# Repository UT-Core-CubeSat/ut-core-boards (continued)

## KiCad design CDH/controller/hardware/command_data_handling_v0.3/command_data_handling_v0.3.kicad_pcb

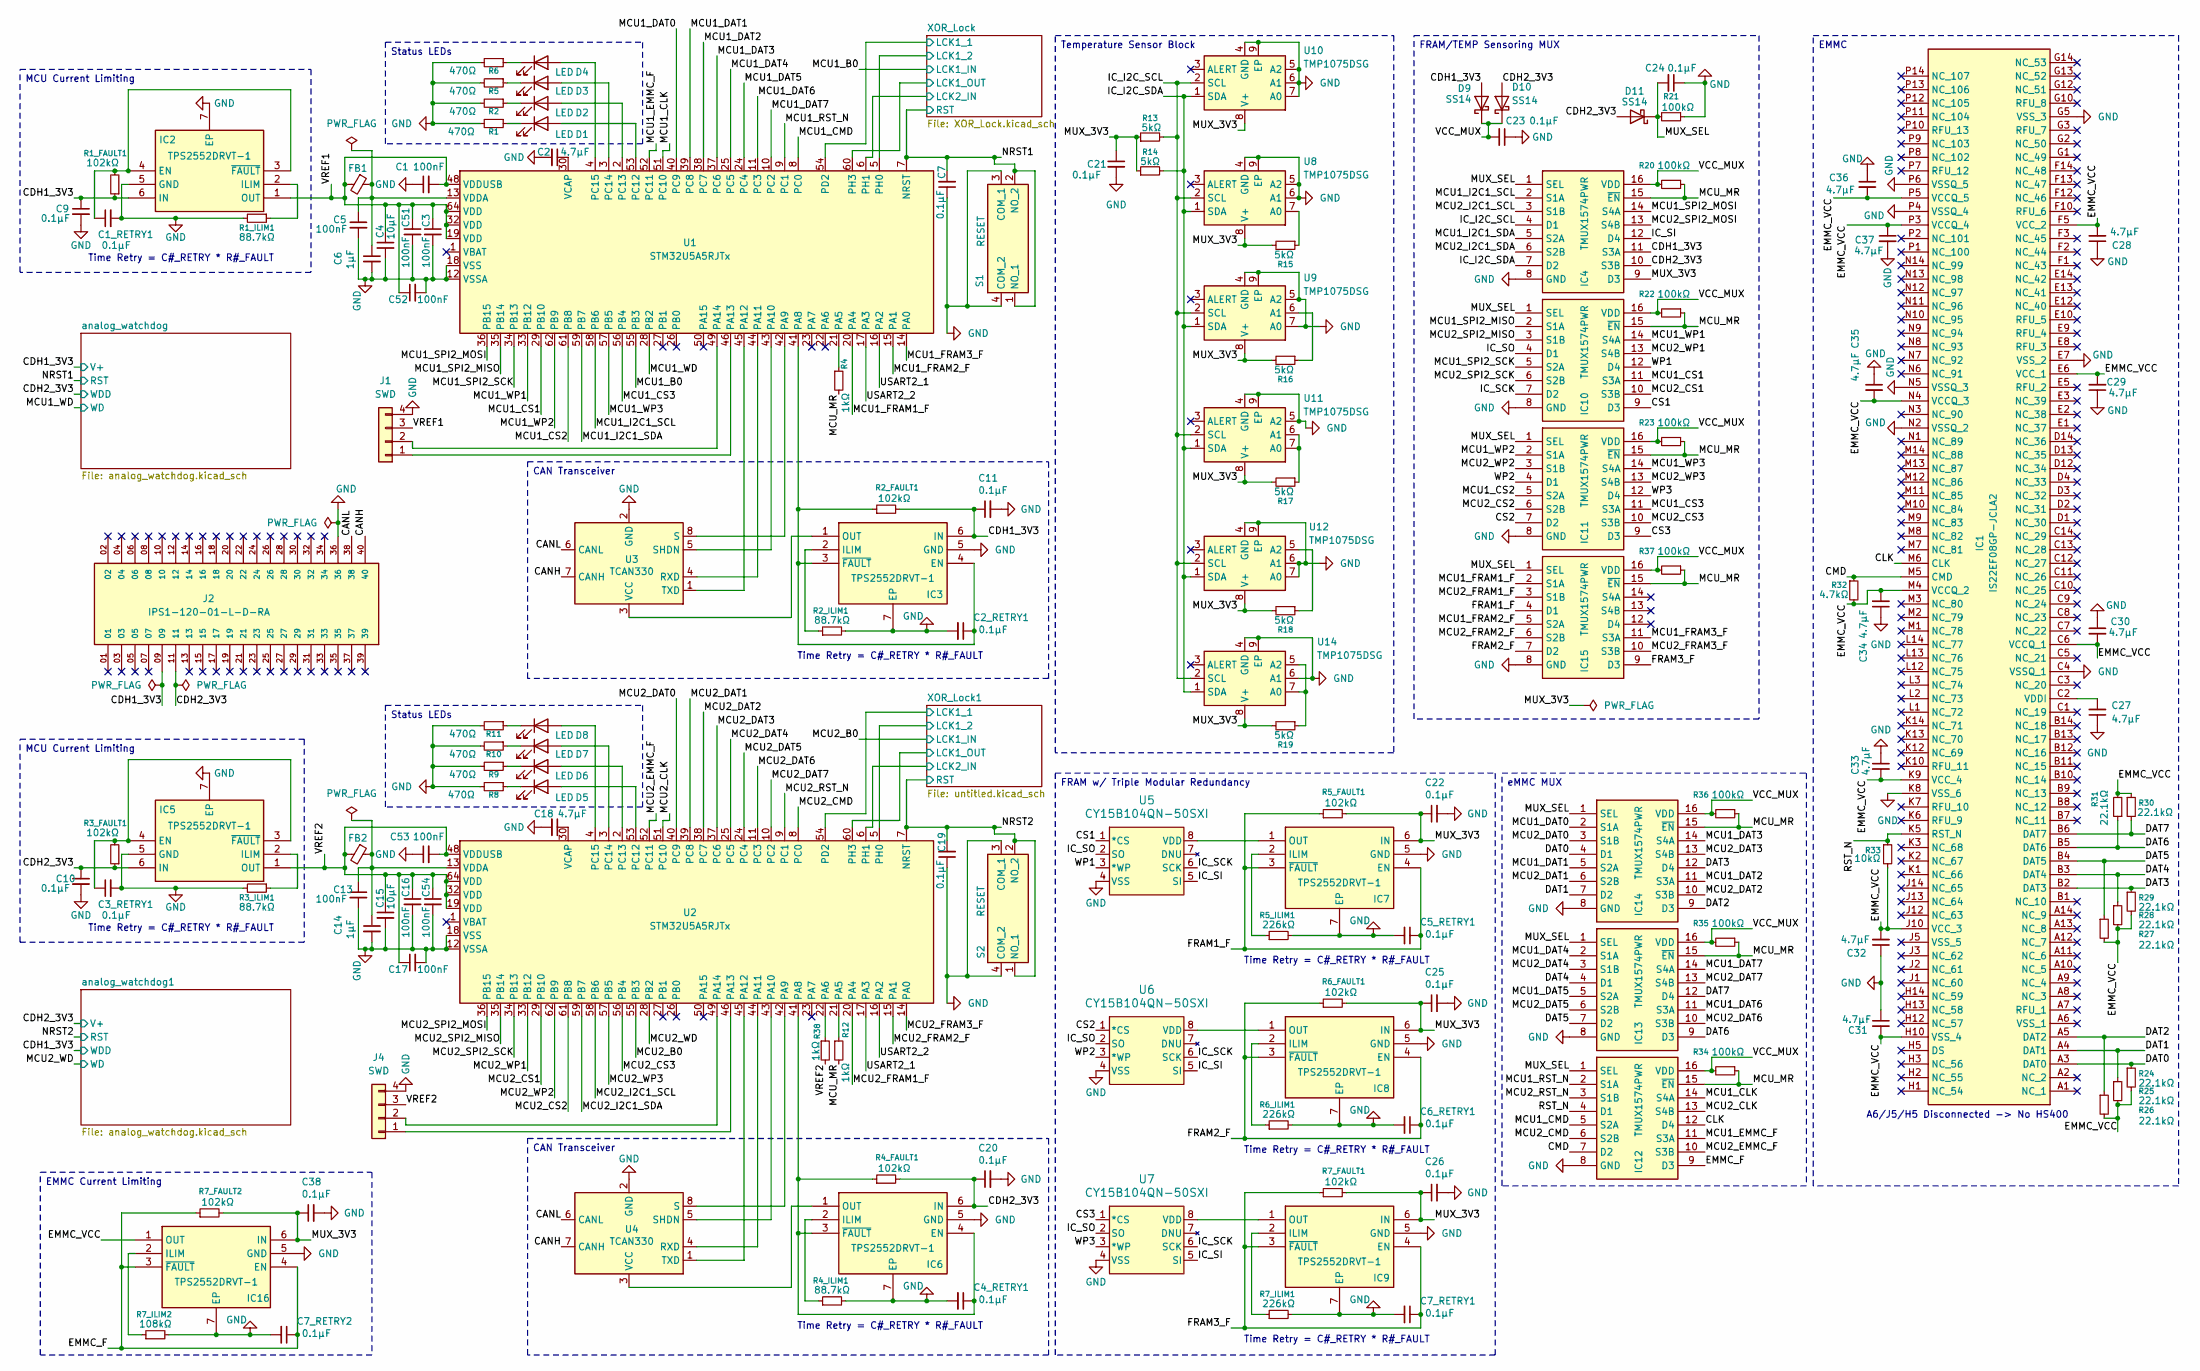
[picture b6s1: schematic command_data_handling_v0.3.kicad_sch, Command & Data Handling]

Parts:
C1, C3, C5, C13, C16, C17, C51, C52, C53, C54: 100nF; C_0603_1608Metric_Pad1.08x0.95mm_HandSolder
C1_RETRY1, C2_RETRY1, C3_RETRY1, C4_RETRY1, C5_RETRY1, C6_RETRY1, C7, C7_RETRY1, C7_RETRY2, C9, C10, C11, C19, C20, C21, C22, C23, C24, C25, C26, C38: 0.1µF; C_0603_1608Metric_Pad1.08x0.95mm_HandSolder
C2, C18, C27, C28, C29, C30, C31, C32, C33, C34, C35, C36, C37: 4.7µF; C_0805_2012Metric_Pad1.18x1.45mm_HandSolder
C4, C15: 10µF; C_0805_2012Metric_Pad1.18x1.45mm_HandSolder
C6, C14: 1µF; C_0805_2012Metric_Pad1.18x1.45mm_HandSolder
D1, D2, D3, D4, D5, D6, D7, D8: LED; LED_0201_0603Metric_Pad0.64x0.40mm_HandSolder
D9, D10, D11: SS14; D_SMA
FB1, FB2: FerriteBead_Small; R_0805_2012Metric_Pad1.20x1.40mm_HandSolder
IC1: IS22EF08GP-JCLA2; Mouser Part Number 870-IS22EF08GP-JCLA2
IC2, IC3, IC5, IC6, IC7, IC8, IC9, IC16: TPS2552DRVT-1; Mouser Part Number 595-TPS2552DRVT-1
IC4, IC10, IC11, IC12, IC13, IC14, IC15: TMUX1574PWR; Mouser Part Number 595-TMUX1574PWR
J1, J4: SWD; PinSocket_1x04_P2.54mm_Vertical
J2: IPS1-120-01-L-D-RA
R1, R2, R5, R6, R8, R9, R10, R11: 470Ω; R_0805_2012Metric_Pad1.20x1.40mm_HandSolder
R1_FAULT1, R2_FAULT1, R3_FAULT1, R4_FAULT1, R5_FAULT1, R6_FAULT1, R7_FAULT1, R7_FAULT2: 102kΩ; R_0805_2012Metric_Pad1.20x1.40mm_HandSolder
R1_ILIM1, R2_ILIM1, R3_ILIM1, R4_ILIM1: 88.7kΩ; R_0805_2012Metric_Pad1.20x1.40mm_HandSolder
R4, R12, R38: 1kΩ; R_0805_2012Metric_Pad1.20x1.40mm_HandSolder
R5_ILIM1, R6_ILIM1, R7_ILIM1: 226kΩ; R_0805_2012Metric_Pad1.20x1.40mm_HandSolder
R7_ILIM2: 108kΩ; R_0805_2012Metric_Pad1.20x1.40mm_HandSolder
R13, R14, R15, R16, R17, R18, R19: 5kΩ; R_0603_1608Metric_Pad0.98x0.95mm_HandSolder
R20, R21, R22, R23, R34, R35, R36, R37: 100kΩ; R_0805_2012Metric_Pad1.20x1.40mm_HandSolder
R24, R25, R26, R27, R28, R29, R30, R31: 22.1kΩ; R_0805_2012Metric_Pad1.20x1.40mm_HandSolder
R32: 4.7kΩ; R_0805_2012Metric_Pad1.20x1.40mm_HandSolder
R33: 10kΩ; R_0805_2012Metric_Pad1.20x1.40mm_HandSolder
S1, S2: RESET; KMR731NGLFS; Mouser Part Number 611-KMR731NGLFS
U1, U2: STM32U5A5RJTx; LQFP-64_10x10mm_P0.5mm
U3, U4: TCAN330; SOIC-8_3.9x4.9mm_P1.27mm
U5, U6, U7: CY15B104QN-50SXI
U8, U9, U10, U11, U12, U14: TMP1075DSG; WSON-8-1EP_2x2mm_P0.5mm_EP0.9x1.6mm_ThermalVias

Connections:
/CANH: J2.40, U3.7 (CANH), U4.7 (CANH)
/CANL: J2.38, U3.6 (CANL), U4.6 (CANL)
/CDH1_3V3: C9.1, C11.1, D9.2 (A), IC2.6 (IN), IC3.6 (IN), IC4.11 (S3A), J2.09, R1_FAULT1.1, R2_FAULT1.2; also elsewhere on the board
/CDH2_3V3: C10.1, C20.1, D10.2 (A), D11.2 (A), IC4.10 (S3B), IC5.6 (IN), IC6.6 (IN), J2.11, R3_FAULT1.1, R4_FAULT1.2; also elsewhere on the board
/CLK: IC1.M6 (CLK), IC12.12 (D4)
/CMD: IC1.M5 (CMD), IC12.7 (D2), R32.1
/CS1: IC10.9 (D3), U5.1 (*CS)
/CS2: IC11.7 (D2), U6.1 (*CS)
/CS3: IC11.9 (D3), U7.1 (*CS)
/DAT0: IC1.A3 (DAT0), IC14.4 (D1), R24.1
/DAT1: IC1.A4 (DAT1), IC14.7 (D2), R25.1
/DAT2: IC1.A5 (DAT2), IC14.9 (D3), R26.1
/DAT3: IC1.B2 (DAT3), IC14.12 (D4), R29.1
/DAT4: IC1.B3 (DAT4), IC13.4 (D1), R28.1
/DAT5: IC1.B4 (DAT5), IC13.7 (D2), R27.1
/DAT6: IC1.B5 (DAT6), IC13.9 (D3), R31.1
/DAT7: IC1.B6 (DAT7), IC13.12 (D4), R30.2
/EMMC_F: C7_RETRY2.1, IC12.9 (D3), IC16.3 (~FAULT), IC16.4 (EN), R7_FAULT2.1
/EMMC_VCC: C28.2, C29.2, C30.2, C31.2, C32.2, C33.2, C34.2, C35.2, C36.2, C37.1, IC1.C6 (VCCQ_1), IC1.E6 (VCC_1), IC1.F5 (VCC_2), IC1.H10 (VSS_4), IC1.J10 (VCC_3), IC1.K9 (VCC_4), IC1.M4 (VCCQ_2), IC1.N4 (VCCQ_3), IC1.P3 (VCCQ_4), IC1.P5 (VCCQ_5), IC16.1 (OUT), R24.2, R25.2, R26.2, R27.2, R28.2, R29.2, R30.1, R31.2, R32.2, R33.2
/FRAM1_F: C5_RETRY1.1, IC7.3 (~FAULT), IC7.4 (EN), IC15.4 (D1), R5_FAULT1.1
/FRAM2_F: C6_RETRY1.1, IC8.3 (~FAULT), IC8.4 (EN), IC15.7 (D2), R6_FAULT1.1
/FRAM3_F: C7_RETRY1.1, IC9.3 (~FAULT), IC9.4 (EN), IC15.9 (D3), R7_FAULT1.1
/IC_I2C_SCL: IC4.4 (D1), R13.2, U8.2 (SCL), U9.2 (SCL), U10.2 (SCL), U11.2 (SCL), U12.2 (SCL), U14.2 (SCL)
/IC_I2C_SDA: IC4.7 (D2), R14.2, U8.1 (SDA), U9.1 (SDA), U10.1 (SDA), U11.1 (SDA), U12.1 (SDA), U14.1 (SDA)
/IC_SCK: IC10.7 (D2), U5.6 (SCK), U6.6 (SCK), U7.6 (SCK)
/IC_SI: IC4.12 (D4), U5.5 (SI), U6.5 (SI), U7.5 (SI)
/IC_SO: IC10.4 (D1), U5.2 (SO), U6.2 (SO), U7.2 (SO)
/MCU1_B0: U1.55 (PB3); also elsewhere on the board
/MCU1_CLK: IC12.14 (S4A), U1.51 (PC10)
/MCU1_CMD: IC12.5 (S2A), U1.8 (PC0)
/MCU1_CS1: IC10.11 (S3A), U1.29 (PB10)
/MCU1_CS2: IC11.5 (S2A), U1.61 (PB8)
/MCU1_CS3: IC11.11 (S3A), U1.56 (PB4)
/MCU1_DAT0: IC14.2 (S1A), U1.40 (PC9)
/MCU1_DAT1: IC14.5 (S2A), U1.39 (PC8)
/MCU1_DAT2: IC14.11 (S3A), U1.38 (PC7)
/MCU1_DAT3: IC14.14 (S4A), U1.37 (PC6)
/MCU1_DAT4: IC13.2 (S1A), U1.25 (PC5)
/MCU1_DAT5: IC13.5 (S2A), U1.24 (PC4)
/MCU1_DAT6: IC13.11 (S3A), U1.11 (PC3)
/MCU1_DAT7: IC13.14 (S4A), U1.10 (PC2)
/MCU1_EMMC_F: IC12.11 (S3A), U1.52 (PC11)
/MCU1_FRAM1_F: IC15.2 (S1A), U1.20 (PA4)
/MCU1_FRAM2_F: IC15.5 (S2A), U1.15 (PA1)
/MCU1_FRAM3_F: IC15.11 (S3A), U1.14 (PA0)
/MCU1_I2C1_SCL: IC4.2 (S1A), U1.58 (PB6)
/MCU1_I2C1_SDA: IC4.5 (S2A), U1.59 (PB7)
/MCU1_RST_N: IC12.2 (S1A), U1.9 (PC1)
/MCU1_SPI2_MISO: IC10.2 (S1A), U1.35 (PB14)
/MCU1_SPI2_MOSI: IC4.14 (S4A), U1.36 (PB15)
/MCU1_SPI2_SCK: IC10.5 (S2A), U1.34 (PB13)
/MCU1_WD: U1.28 (PB2); also elsewhere on the board
/MCU1_WP1: IC10.14 (S4A), U1.33 (PB12)
/MCU1_WP2: IC11.2 (S1A), U1.62 (PB9)
/MCU1_WP3: IC11.14 (S4A), U1.57 (PB5)
/MCU2_B0: U2.55 (PB3); also elsewhere on the board
/MCU2_CLK: IC12.13 (S4B), U2.51 (PC10)
/MCU2_CMD: IC12.6 (S2B), U2.8 (PC0)
/MCU2_CS1: IC10.10 (S3B), U2.29 (PB10)
/MCU2_CS2: IC11.6 (S2B), U2.61 (PB8)
/MCU2_CS3: IC11.10 (S3B), U2.56 (PB4)
/MCU2_DAT0: IC14.3 (S1B), U2.40 (PC9)
/MCU2_DAT1: IC14.6 (S2B), U2.39 (PC8)
/MCU2_DAT2: IC14.10 (S3B), U2.38 (PC7)
/MCU2_DAT3: IC14.13 (S4B), U2.37 (PC6)
/MCU2_DAT4: IC13.3 (S1B), U2.25 (PC5)
/MCU2_DAT5: IC13.6 (S2B), U2.24 (PC4)
/MCU2_DAT6: IC13.10 (S3B), U2.11 (PC3)
/MCU2_DAT7: IC13.13 (S4B), U2.10 (PC2)
/MCU2_EMMC_F: IC12.10 (S3B), U2.52 (PC11)
/MCU2_FRAM1_F: IC15.3 (S1B), U2.20 (PA4)
/MCU2_FRAM2_F: IC15.6 (S2B), U2.15 (PA1)
/MCU2_FRAM3_F: IC15.10 (S3B), U2.14 (PA0)
/MCU2_I2C1_SCL: IC4.3 (S1B), U2.58 (PB6)
/MCU2_I2C1_SDA: IC4.6 (S2B), U2.59 (PB7)
/MCU2_RST_N: IC12.3 (S1B), U2.9 (PC1)
/MCU2_SPI2_MISO: IC10.3 (S1B), U2.35 (PB14)
/MCU2_SPI2_MOSI: IC4.13 (S4B), U2.36 (PB15)
/MCU2_SPI2_SCK: IC10.6 (S2B), U2.34 (PB13)
/MCU2_WD: U2.28 (PB2); also elsewhere on the board
/MCU2_WP1: IC10.13 (S4B), U2.33 (PB12)
/MCU2_WP2: IC11.3 (S1B), U2.62 (PB9)
/MCU2_WP3: IC11.13 (S4B), U2.57 (PB5)
/MCU_MR: IC4.15 (~EN), IC10.15 (~EN), IC11.15 (~EN), IC12.15 (~EN), IC13.15 (~EN), IC14.15 (~EN), IC15.15 (~EN), R4.2, R12.2, R20.1, R22.1, R23.1, R34.1, R35.1, R36.1, R37.1
/MUX_3V3: C21.1, C22.1, C25.1, C26.1, C38.1, IC4.9 (D3), IC7.6 (IN), IC8.6 (IN), IC9.6 (IN), IC16.6 (IN), R5_FAULT1.2, R6_FAULT1.2, R7_FAULT1.2, R7_FAULT2.2, R13.1, R14.1, R15.2, R16.2, R17.2, R18.2, R19.2, U8.8 (V+), U9.8 (V+), U10.8 (V+), U11.8 (V+), U12.8 (V+), U14.8 (V+)
/MUX_SEL: C24.2, D11.1 (K), IC4.1 (SEL), IC10.1 (SEL), IC11.1 (SEL), IC12.1 (SEL), IC13.1 (SEL), IC14.1 (SEL), IC15.1 (SEL), R21.2
/NRST1: C7.2, S1.1 (NO_1), S1.2 (NO_2), U1.7 (NRST); also elsewhere on the board
/NRST2: C19.2, S2.1 (NO_1), S2.2 (NO_2), U2.7 (NRST); also elsewhere on the board
/RST_N: IC1.K5 (RST_N), IC12.4 (D1), R33.1
/USART2_1: U1.16 (PA2), U2.17 (PA3)
/USART2_2: U1.17 (PA3), U2.16 (PA2)
/VCC_MUX: C23.2, D9.1 (K), D10.1 (K), IC4.16 (VDD), IC10.16 (VDD), IC11.16 (VDD), IC12.16 (VDD), IC13.16 (VDD), IC14.16 (VDD), IC15.16 (VDD), R20.2, R22.2, R23.2, R34.2, R35.2, R36.2, R37.2
/VREF1: C1.2, C3.1, C4.1, C51.1, C52.1, FB1.2, IC2.1 (OUT), J1.3, U1.19 (VDD), U1.32 (VDD), U1.48 (VDDUSB), U1.64 (VDD)
/VREF2: C15.1, C16.1, C17.1, C53.2, C54.1, FB2.2, IC5.1 (OUT), J4.3, R38.2, U2.19 (VDD), U2.32 (VDD), U2.48 (VDDUSB), U2.64 (VDD)
/WP1: IC10.12 (D4), U5.3 (*WP)
/WP2: IC11.4 (D1), U6.3 (*WP)
/WP3: IC11.12 (D4), U7.3 (*WP)
/XOR_Lock1/LCK1_1: U2.54 (PD2); also elsewhere on the board
/XOR_Lock1/LCK1_2: U2.5 (PH0); also elsewhere on the board
/XOR_Lock1/LCK1_OUT: U2.60 (PH3); also elsewhere on the board
/XOR_Lock1/LCK2_IN: U2.6 (PH1); also elsewhere on the board
/XOR_Lock/LCK1_1: U1.54 (PD2); also elsewhere on the board
/XOR_Lock/LCK1_2: U1.5 (PH0); also elsewhere on the board
/XOR_Lock/LCK1_OUT: U1.60 (PH3); also elsewhere on the board
/XOR_Lock/LCK2_IN: U1.6 (PH1); also elsewhere on the board
GND: C1.1, C1_RETRY1.2, C2.2, C2_RETRY1.2, C3.2, C3_RETRY1.2, C4.2, C4_RETRY1.2, C5.2, C5_RETRY1.2, C6.2, C6_RETRY1.2, C7.1, C7_RETRY1.2, C7_RETRY2.2, C9.2, C10.2, C11.2, C13.2, C14.2, C15.2, C16.2, C17.2, C18.2, C19.1, C20.2, C21.2, C22.2, C23.1, C24.1, C25.2, C26.2, C27.1, C28.1, C29.1, C30.1, C31.1, C32.1, C33.1, C34.1, C35.1, C36.1, C37.2, C38.2, C51.2, C52.2, C53.1, C54.2, IC1.C4 (VSSQ_1), IC1.E7 (VSS_2), IC1.G5 (VSS_3), IC1.K8 (VSS_6), IC1.N2 (VSSQ_2), IC1.N5 (VSSQ_3), IC1.P4 (VSSQ_4), IC1.P6 (VSSQ_5), IC2.5 (GND), IC2.7 (EP), IC3.5 (GND), IC3.7 (EP), IC4.8 (GND), IC5.5 (GND), IC5.7 (EP), IC6.5 (GND), IC6.7 (EP), IC7.5 (GND), IC7.7 (EP), IC8.5 (GND), IC8.7 (EP), IC9.5 (GND), IC9.7 (EP), IC10.8 (GND), IC11.8 (GND), IC12.8 (GND), IC13.8 (GND), IC14.8 (GND), IC15.8 (GND), IC16.5 (GND), IC16.7 (EP), J1.4, J2.36, J4.4, R1.2, R1_ILIM1.2, R2.2, R2_ILIM1.2, R3_ILIM1.2, R4_ILIM1.2, R5.2, R5_ILIM1.2, R6.2, R6_ILIM1.2, R7_ILIM1.2, R7_ILIM2.2, R8.2, R9.2, R10.2, R11.2, R21.1, S1.3 (COM_1), S1.4 (COM_2), S2.3 (COM_1), S2.4 (COM_2), U1.12 (VSSA), U1.18 (VSS), U1.31 (VSS), U1.47 (VSS), U1.63 (VSS), U2.12 (VSSA), U2.18 (VSS), U2.31 (VSS), U2.47 (VSS), U2.63 (VSS), U3.2 (GND), U4.2 (GND), U5.4 (VSS), U6.4 (VSS), U7.4 (VSS), U8.4 (GND), U8.5 (A2), U8.6 (A1), U8.9 (EP), U9.4 (GND), U9.5 (A2), U9.7 (A0), U9.9 (EP), U10.4 (GND), U10.5 (A2), U10.6 (A1), U10.7 (A0), U10.9 (EP), U11.4 (GND), U11.5 (A2), U11.9 (EP), U12.4 (GND), U12.6 (A1), U12.7 (A0), U12.9 (EP), U14.4 (GND), U14.6 (A1), U14.9 (EP); also elsewhere on the board
unnamed: D1.2 (A), U1.53 (PC12)
unnamed: D1.1 (K), R1.1
unnamed: D2.2 (A), U1.2 (PC13)
unnamed: D2.1 (K), R2.1
unnamed: D3.2 (A), U1.3 (PC14)
unnamed: D3.1 (K), R5.1
unnamed: D4.2 (A), U1.4 (PC15)
unnamed: D4.1 (K), R6.1
unnamed: D5.2 (A), U2.53 (PC12)
unnamed: D5.1 (K), R8.1
unnamed: D6.2 (A), U2.2 (PC13)
unnamed: D6.1 (K), R9.1
unnamed: D7.2 (A), U2.3 (PC14)
unnamed: D7.1 (K), R10.1
unnamed: D8.2 (A), U2.4 (PC15)
unnamed: D8.1 (K), R11.1
unnamed: C27.2, IC1.C2 (VDDI)
unnamed: C1_RETRY1.1, IC2.3 (~FAULT), IC2.4 (EN), R1_FAULT1.2
unnamed: IC2.2 (ILIM), R1_ILIM1.1
unnamed: C2_RETRY1.1, IC3.3 (~FAULT), IC3.4 (EN), R2_FAULT1.1, U1.41 (PA8)
unnamed: IC3.2 (ILIM), R2_ILIM1.1
unnamed: IC3.1 (OUT), U3.3 (VCC)
unnamed: C3_RETRY1.1, IC5.3 (~FAULT), IC5.4 (EN), R3_FAULT1.2
unnamed: IC5.2 (ILIM), R3_ILIM1.1
unnamed: C4_RETRY1.1, IC6.3 (~FAULT), IC6.4 (EN), R4_FAULT1.1, U2.41 (PA8)
unnamed: IC6.2 (ILIM), R4_ILIM1.1
unnamed: IC6.1 (OUT), U4.3 (VCC)
unnamed: IC7.2 (ILIM), R5_ILIM1.1
unnamed: IC7.1 (OUT), U5.8 (VDD)
unnamed: IC8.2 (ILIM), R6_ILIM1.1
unnamed: IC8.1 (OUT), U6.8 (VDD)
unnamed: IC9.2 (ILIM), R7_ILIM1.1
unnamed: IC9.1 (OUT), U7.8 (VDD)
unnamed: IC16.2 (ILIM), R7_ILIM2.1
unnamed: J1.1, U1.46 (PA13)
unnamed: J1.2, U1.49 (PA14)
unnamed: J4.1, U2.46 (PA13)
unnamed: J4.2, U2.49 (PA14)
unnamed: R4.1, U1.21 (PA5)
unnamed: U1.42 (PA9), U3.8 (S)
unnamed: U1.43 (PA10), U3.5 (SHDN)
unnamed: U1.44 (PA11), U3.4 (RXD)
unnamed: U1.45 (PA12), U3.1 (TXD)
unnamed: C2.1, U1.30 (VCAP)
unnamed: C5.1, C6.1, FB1.1, U1.13 (VDDA)
unnamed: R12.1, U2.21 (PA5)
unnamed: R38.1, U2.22 (PA6)
unnamed: U2.42 (PA9), U4.8 (S)
unnamed: U2.43 (PA10), U4.5 (SHDN)
unnamed: U2.44 (PA11), U4.4 (RXD)
unnamed: U2.45 (PA12), U4.1 (TXD)
unnamed: C18.1, U2.30 (VCAP)
unnamed: C13.1, C14.1, FB2.1, U2.13 (VDDA)
unnamed: R15.1, U8.7 (A0)
unnamed: R16.1, U9.6 (A1)
unnamed: R17.1, U11.6 (A1), U11.7 (A0)
unnamed: R18.1, U12.5 (A2)
unnamed: R19.1, U14.5 (A2), U14.7 (A0)

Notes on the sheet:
Time Retry = C#_RETRY * R#_FAULT
A6/J5/H5 Disconnected -> No HS400
Status LEDs
CAN Transceiver
EMMC
Temperature Sensor Block
FRAM w/ Triple Modular Redundancy
FRAM/TEMP Sensoring MUX
eMMC MUX
EMMC Current Limiting
MCU Current Limiting

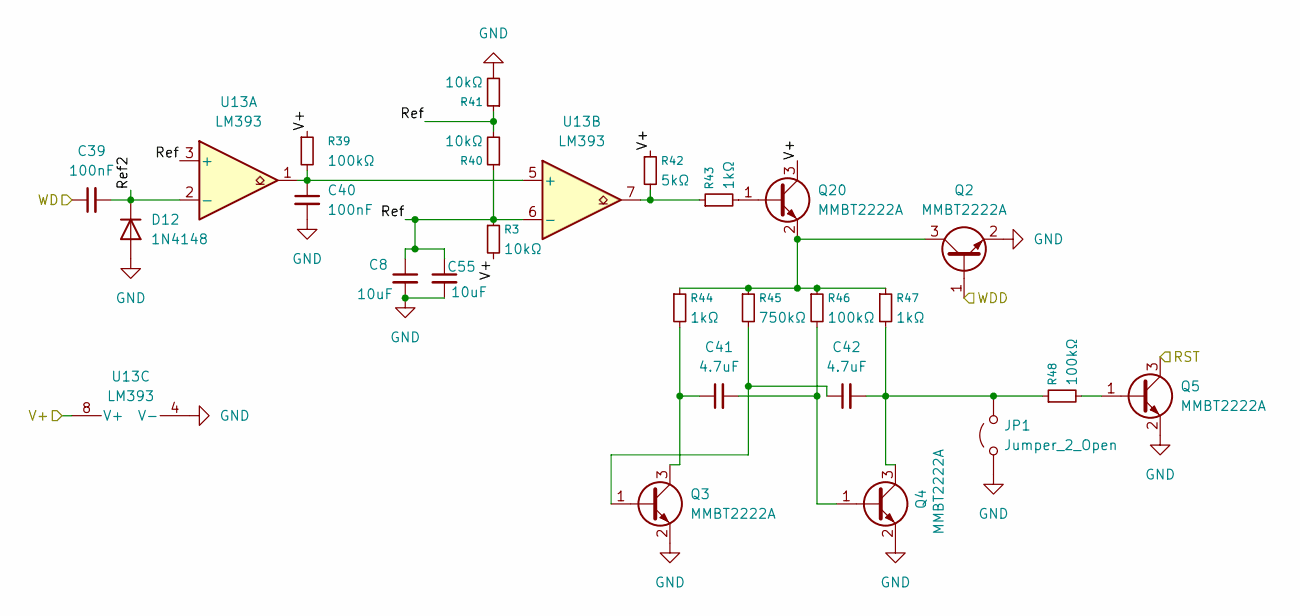
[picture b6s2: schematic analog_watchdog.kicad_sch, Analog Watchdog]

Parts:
C8, C55: 10uF; C_0805_2012Metric_Pad1.18x1.45mm_HandSolder
C39, C40: 100nF; C_0805_2012Metric_Pad1.18x1.45mm_HandSolder
C41, C42: 4.7uF; C_0805_2012Metric_Pad1.18x1.45mm_HandSolder
D12: 1N4148; D_DO-35_SOD27_P7.62mm_Horizontal
JP1: Jumper_2_Open; TestPoint_2Pads_Pitch2.54mm_Drill0.8mm
Q2, Q3, Q4, Q5, Q20: MMBT2222A; SOT-23
R3, R40, R41: 10kΩ; R_0805_2012Metric_Pad1.20x1.40mm_HandSolder
R39, R46, R48: 100kΩ; R_0805_2012Metric_Pad1.20x1.40mm_HandSolder
R42: 5kΩ; R_0805_2012Metric_Pad1.20x1.40mm_HandSolder
R43, R44, R47: 1kΩ; R_0805_2012Metric_Pad1.20x1.40mm_HandSolder
R45: 750kΩ; R_0805_2012Metric_Pad1.20x1.40mm_HandSolder
U13: LM393; SOIC-8_3.9x4.9mm_P1.27mm

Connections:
/CDH1_3V3: Q20.3 (C), R3.2, R39.1, R42.1, U13.8 (V+); also elsewhere on the board
/CDH2_3V3: Q2.1 (B); also elsewhere on the board
/MCU1_WD: C39.1; also elsewhere on the board
/NRST1: Q5.3 (C); also elsewhere on the board
GND: C8.2, C40.2, C55.2, D12.2 (A), JP1.1 (A), Q2.2 (E), Q3.2 (E), Q4.2 (E), Q5.2 (E), R41.2, U13.4 (V-); also elsewhere on the board
unnamed: C42.2, JP1.2 (B), Q4.3 (C), R47.2, R48.1
unnamed: Q2.3 (C), Q20.2 (E), R44.1, R45.1, R46.1, R47.1
unnamed: C42.1, Q3.1 (B), R45.2
unnamed: C41.1, Q3.3 (C), R44.2
unnamed: C41.2, Q4.1 (B), R46.2
unnamed: Q5.1 (B), R48.2
unnamed: Q20.1 (B), R43.2
unnamed: R42.2, R43.1, U13.7
unnamed: C40.1, R39.2, U13.1, U13.5 (+)

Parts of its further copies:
C12, C43: 100nF; C_0805_2012Metric_Pad1.18x1.45mm_HandSolder
C44, C56: 10uF; C_0805_2012Metric_Pad1.18x1.45mm_HandSolder
C45, C46: 4.7uF; C_0805_2012Metric_Pad1.18x1.45mm_HandSolder
D13: 1N4148; D_DO-35_SOD27_P7.62mm_Horizontal
JP2: Jumper_2_Open; TestPoint_2Pads_Pitch2.54mm_Drill0.8mm
Q6, Q7, Q8, Q9, Q10: MMBT2222A; SOT-23
R7, R56, R58: 100kΩ; R_0805_2012Metric_Pad1.20x1.40mm_HandSolder
R49, R50, R51: 10kΩ; R_0805_2012Metric_Pad1.20x1.40mm_HandSolder
R52: 5kΩ; R_0805_2012Metric_Pad1.20x1.40mm_HandSolder
R53, R54, R57: 1kΩ; R_0805_2012Metric_Pad1.20x1.40mm_HandSolder
R55: 750kΩ; R_0805_2012Metric_Pad1.20x1.40mm_HandSolder
U15: LM393; SOIC-8_3.9x4.9mm_P1.27mm

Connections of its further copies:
/CDH1_3V3: Q9.1 (B); also elsewhere on the board
/CDH2_3V3: Q7.3 (C), R7.1, R51.2, R52.1, U15.8 (V+); also elsewhere on the board
/MCU2_WD: C12.1; also elsewhere on the board
/NRST2: Q10.3 (C); also elsewhere on the board
/analog_watchdog1/Ref: C44.1, C56.1, R50.1, R51.1, U15.3 (+), U15.6 (-)
/analog_watchdog1/Ref2: C12.2, D13.1 (K), R49.1, R50.2, U15.2 (-)
GND: C43.2, C44.2, C56.2, D13.2 (A), JP2.1 (A), Q6.2 (E), Q8.2 (E), Q9.2 (E), Q10.2 (E), R49.2, U15.4 (V-); also elsewhere on the board
unnamed: C46.2, JP2.2 (B), Q8.3 (C), R57.2, R58.1
unnamed: C46.1, Q6.1 (B), R55.2
unnamed: C45.1, Q6.3 (C), R53.2
unnamed: Q7.1 (B), R54.2
unnamed: Q7.2 (E), Q9.3 (C), R53.1, R55.1, R56.1, R57.1
unnamed: C45.2, Q8.1 (B), R56.2
unnamed: Q10.1 (B), R58.2
unnamed: R52.2, R54.1, U15.7
unnamed: C43.1, R7.2, U15.1, U15.5 (+)

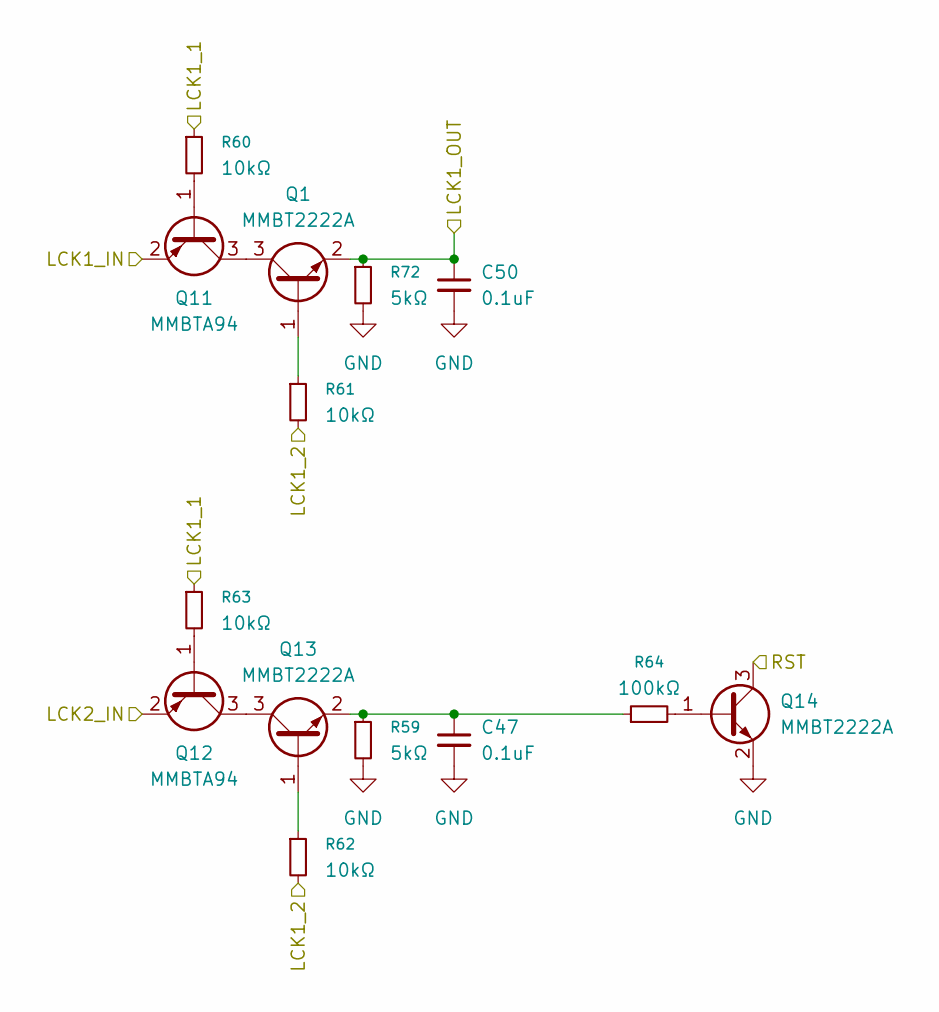
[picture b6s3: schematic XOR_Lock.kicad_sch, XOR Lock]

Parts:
C47, C50: 0.1uF; C_0805_2012Metric_Pad1.18x1.45mm_HandSolder
Q1, Q13, Q14: MMBT2222A; SOT-23
Q11, Q12: MMBTA94; SOT-23
R59, R72: 5kΩ; R_0805_2012Metric_Pad1.20x1.40mm_HandSolder
R60, R61, R62, R63: 10kΩ; R_0805_2012Metric_Pad1.20x1.40mm_HandSolder
R64: 100kΩ; R_0805_2012Metric_Pad1.20x1.40mm_HandSolder

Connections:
/MCU1_B0: Q11.2 (E); also elsewhere on the board
/NRST1: Q14.3 (C); also elsewhere on the board
/XOR_Lock/LCK1_1: R60.1, R63.1; also elsewhere on the board
/XOR_Lock/LCK1_2: R61.2, R62.2; also elsewhere on the board
/XOR_Lock/LCK1_OUT: C50.1, Q1.2 (E), R72.1; also elsewhere on the board
/XOR_Lock/LCK2_IN: Q12.2 (E); also elsewhere on the board
GND: C47.2, C50.2, Q14.2 (E), R59.2, R72.2; also elsewhere on the board
unnamed: Q1.1 (B), R61.1
unnamed: Q1.3 (C), Q11.3 (C)
unnamed: Q11.1 (B), R60.2
unnamed: Q12.1 (B), R63.2
unnamed: Q12.3 (C), Q13.3 (C)
unnamed: Q13.1 (B), R62.1
unnamed: C47.1, Q13.2 (E), R59.1, R64.1
unnamed: Q14.1 (B), R64.2

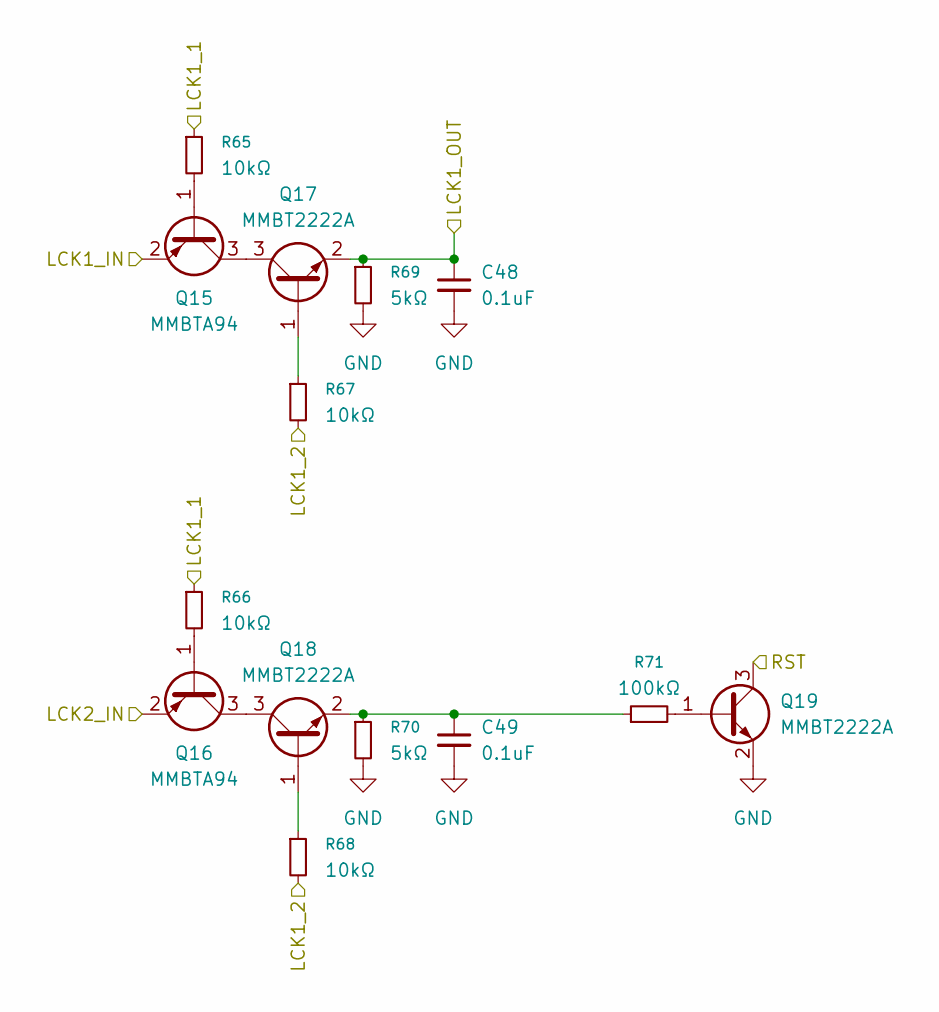
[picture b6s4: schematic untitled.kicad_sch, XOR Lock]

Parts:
C48, C49: 0.1uF; C_0805_2012Metric_Pad1.18x1.45mm_HandSolder
Q15, Q16: MMBTA94; SOT-23
Q17, Q18, Q19: MMBT2222A; SOT-23
R65, R66, R67, R68: 10kΩ; R_0805_2012Metric_Pad1.20x1.40mm_HandSolder
R69, R70: 5kΩ; R_0805_2012Metric_Pad1.20x1.40mm_HandSolder
R71: 100kΩ; R_0805_2012Metric_Pad1.20x1.40mm_HandSolder

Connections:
/MCU2_B0: Q15.2 (E); also elsewhere on the board
/NRST2: Q19.3 (C); also elsewhere on the board
/XOR_Lock1/LCK1_1: R65.1, R66.1; also elsewhere on the board
/XOR_Lock1/LCK1_2: R67.2, R68.2; also elsewhere on the board
/XOR_Lock1/LCK1_OUT: C48.1, Q17.2 (E), R69.1; also elsewhere on the board
/XOR_Lock1/LCK2_IN: Q16.2 (E); also elsewhere on the board
GND: C48.2, C49.2, Q19.2 (E), R69.2, R70.2; also elsewhere on the board
unnamed: Q15.1 (B), R65.2
unnamed: Q15.3 (C), Q17.3 (C)
unnamed: Q16.1 (B), R66.2
unnamed: Q16.3 (C), Q18.3 (C)
unnamed: Q17.1 (B), R67.1
unnamed: Q18.1 (B), R68.1
unnamed: C49.1, Q18.2 (E), R70.1, R71.1
unnamed: Q19.1 (B), R71.2

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
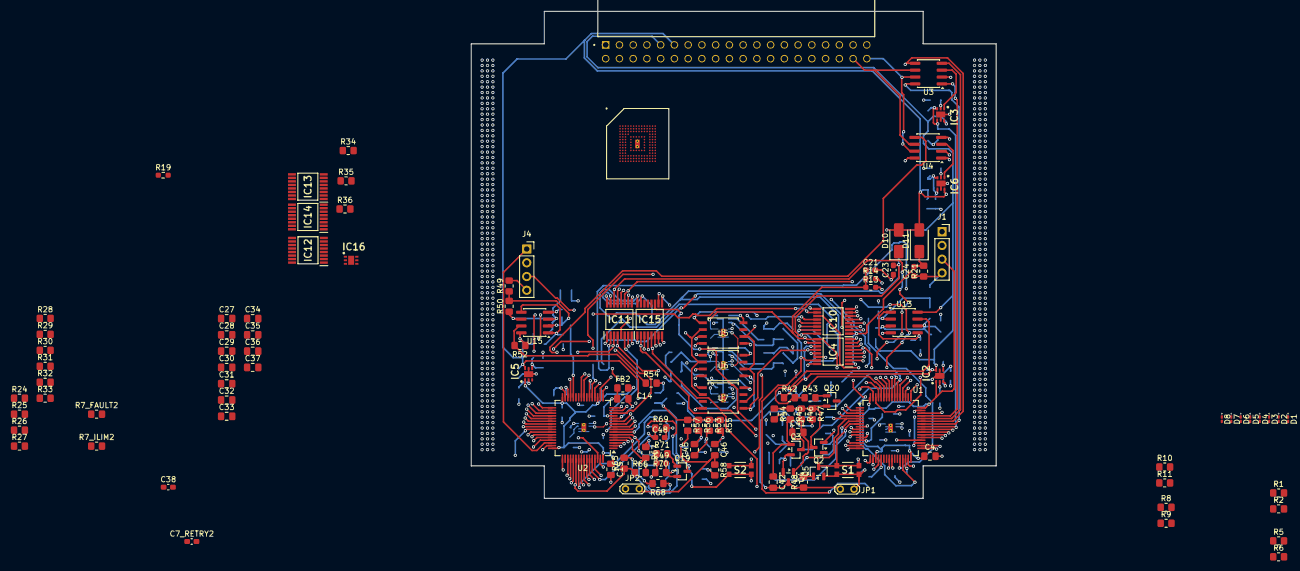
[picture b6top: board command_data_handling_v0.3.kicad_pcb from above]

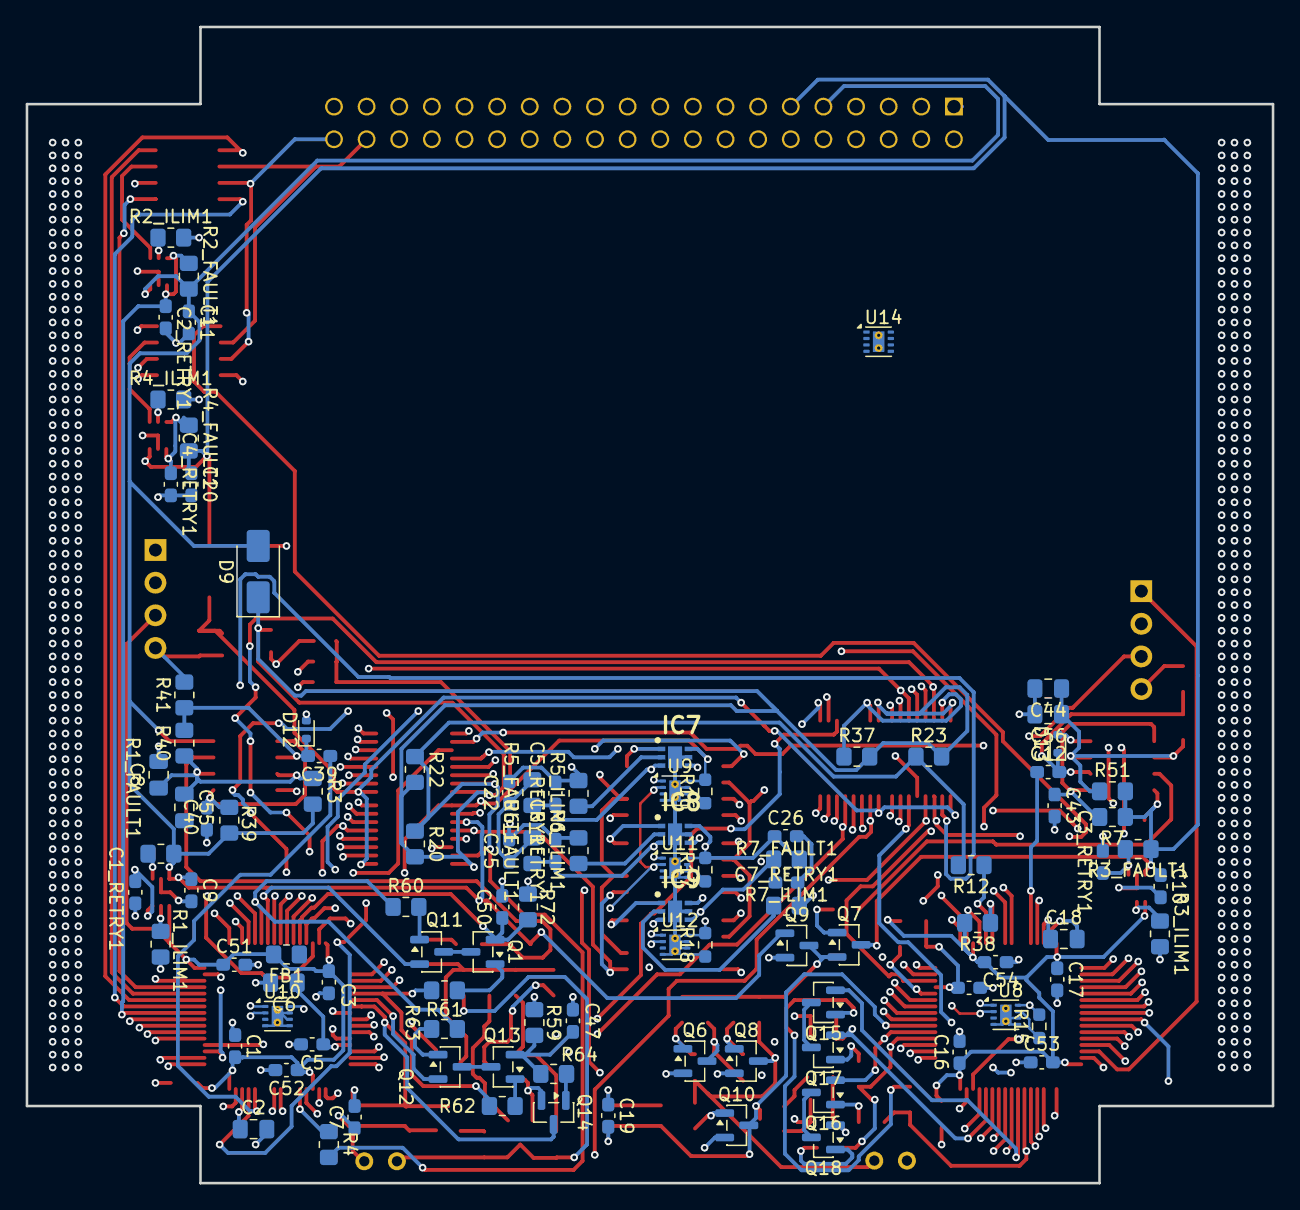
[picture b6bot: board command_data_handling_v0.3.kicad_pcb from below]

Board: 4 copper layers, 97.0 x 90.0 mm, 225 parts (104 on the bottom side), 202 nets.
